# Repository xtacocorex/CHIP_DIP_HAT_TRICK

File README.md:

# CHIP_DIP_HAT_TRICK
CHIP DIP to allow users to attach PI Hats to their CHIP

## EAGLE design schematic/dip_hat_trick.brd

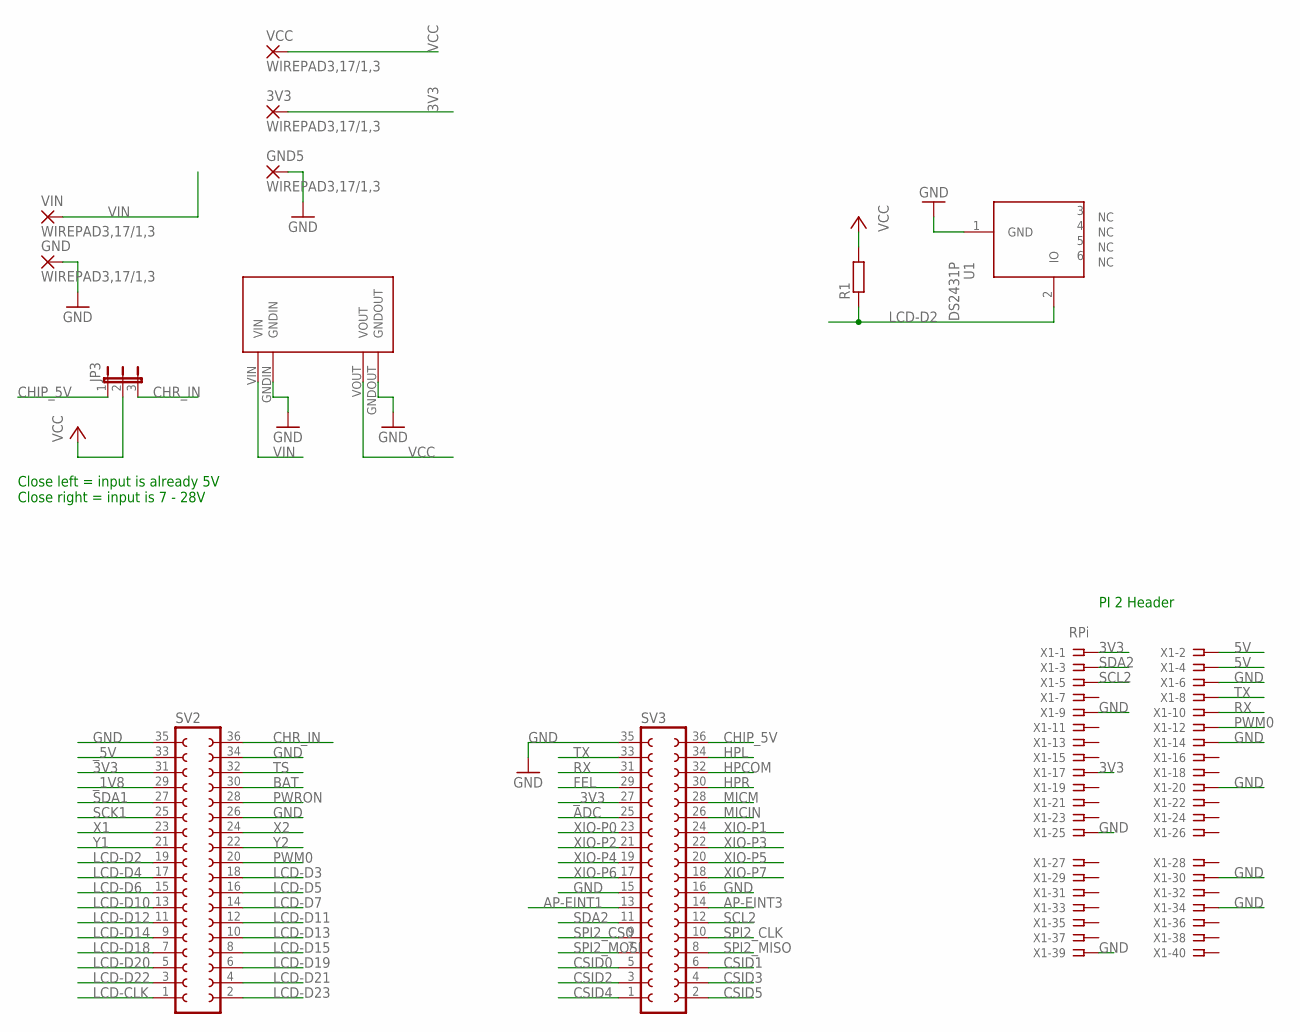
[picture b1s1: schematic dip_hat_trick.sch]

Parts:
3V3: WIREPAD3,17/1,3; 3,17/1,3
GND, GND5: WIREPAD3,17/1,3; 3,17/1,3
JP3: JP2E; JP2
R1: R-EU_R0805; R0805
SV2, SV3: FE18-2
U1: DS2431P; TSOC6
U$9: MP1584EN_FRAMELESS
VCC: WIREPAD3,17/1,3; 3,17/1,3
VIN: WIREPAD3,17/1,3; 3,17/1,3
X1: RPi; SSW-120-02-S-D

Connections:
3V3: 3V3.1, SV2.31, X1.1, X1.17
5V: X1.2, X1.4
ADC: SV3.25
AP-EINT1: SV3.13
AP-EINT3: SV3.14
BAT: SV2.30
CHIP_5V: JP3.1, SV3.36
CHR_IN: JP3.3, SV2.36
CSID0: SV3.5
CSID1: SV3.6
CSID2: SV3.3
CSID3: SV3.4
CSID4: SV3.1
CSID5: SV3.2
FEL: SV3.29
GND: GND.1, GND5.1, SV2.26, SV2.34, SV2.35, SV3.15, SV3.16, SV3.35, U1.1 (GND), U$9.GNDIN, U$9.GNDOUT, X1.6, X1.9, X1.14, X1.20, X1.25, X1.30, X1.34, X1.39
HPCOM: SV3.32
HPL: SV3.34
HPR: SV3.30
LCD-CLK: SV2.1
LCD-D2: R1.1, SV2.19, U1.2 (IO)
LCD-D3: SV2.18
LCD-D4: SV2.17
LCD-D5: SV2.16
LCD-D6: SV2.15
LCD-D7: SV2.14
LCD-D10: SV2.13
LCD-D11: SV2.12
LCD-D12: SV2.11
LCD-D13: SV2.10
LCD-D14: SV2.9
LCD-D15: SV2.8
LCD-D18: SV2.7
LCD-D19: SV2.6
LCD-D20: SV2.5
LCD-D21: SV2.4
LCD-D22: SV2.3
LCD-D23: SV2.2
MICIN: SV3.26
MICM: SV3.28
PWM0: SV2.20, X1.12
PWRON: SV2.28
RX: SV3.31, X1.10
SCK1: SV2.25
SCL2: SV3.12, X1.5
SDA1: SV2.27
SDA2: SV3.11, X1.3
SPI2_CLK: SV3.10
SPI2_CS0: SV3.9
SPI2_MISO: SV3.8
SPI2_MOSI: SV3.7
TS: SV2.32
TX: SV3.33, X1.8
VCC: JP3.2, R1.2, U$9.VOUT, VCC.1
VIN: U$9.VIN, VIN.1
X1: SV2.23
X2: SV2.24
XIO-P0: SV3.23
XIO-P1: SV3.24
XIO-P2: SV3.21
XIO-P3: SV3.22
XIO-P4: SV3.19
XIO-P5: SV3.20
XIO-P6: SV3.17
XIO-P7: SV3.18
Y1: SV2.21
Y2: SV2.22
_1V8: SV2.29
_3V3: SV3.27
_5V: SV2.33

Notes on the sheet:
Close left = input is already 5V Close right = input is 7 - 28V
PI 2 Header

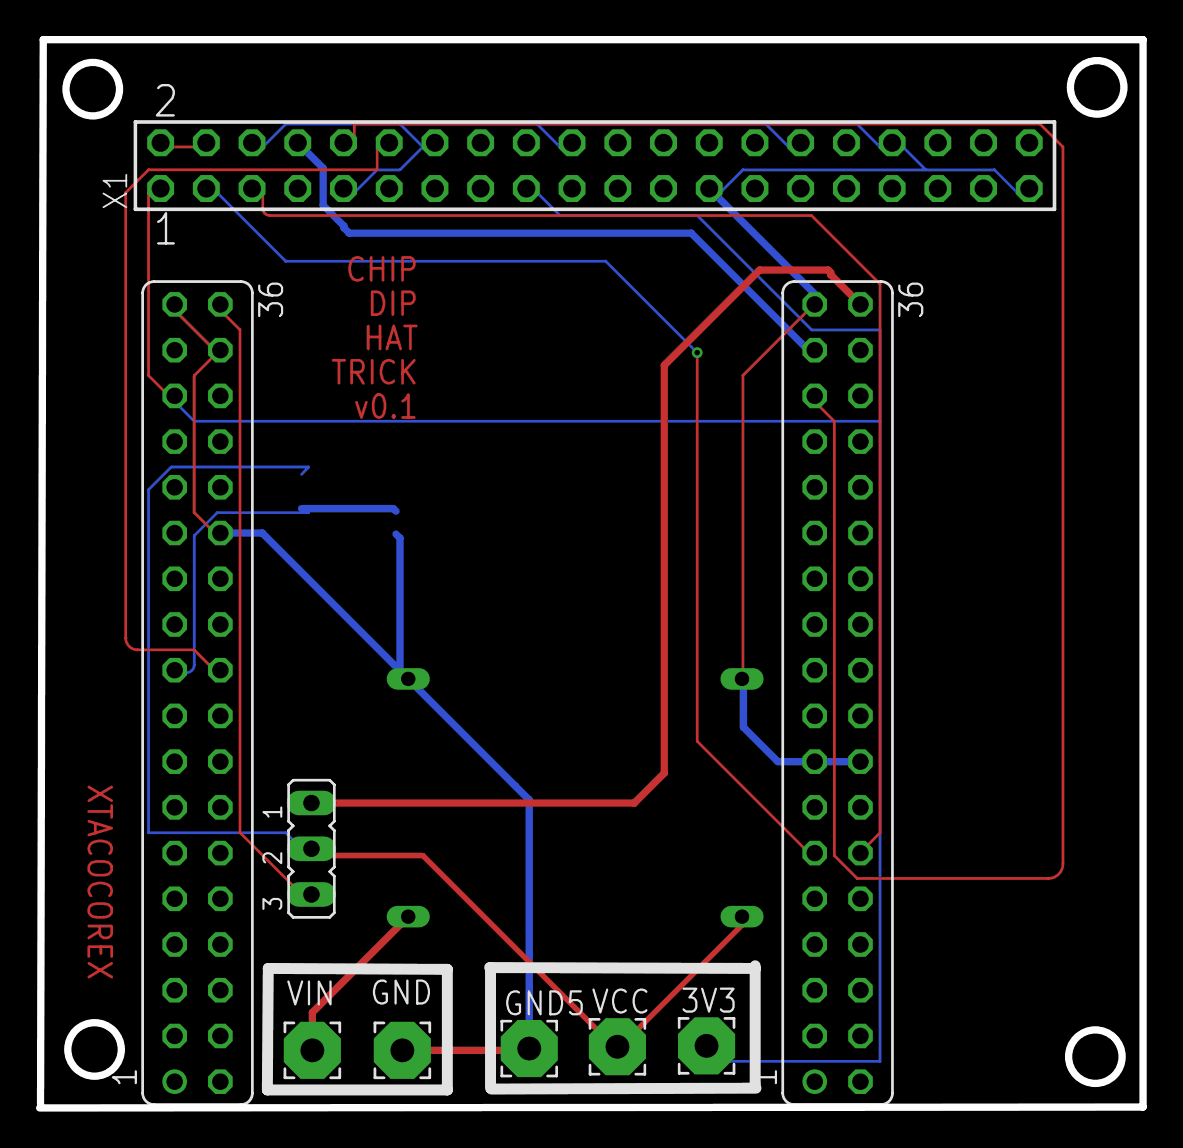
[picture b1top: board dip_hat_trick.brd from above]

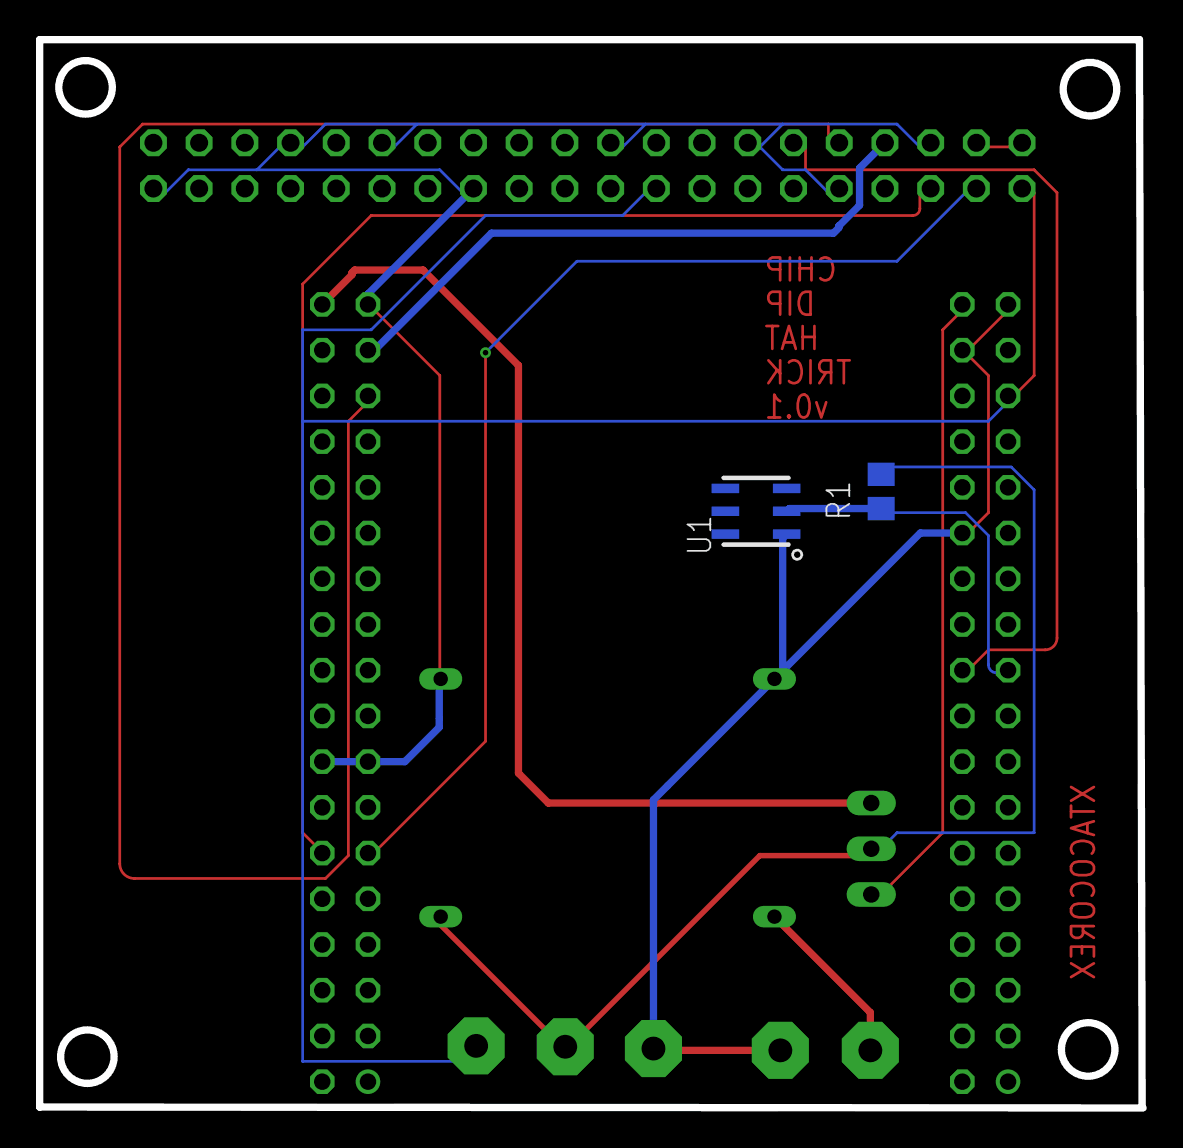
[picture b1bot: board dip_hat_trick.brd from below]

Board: 2 copper layers, 61.3 x 59.3 mm, 12 parts (2 on the bottom side), 13 nets.

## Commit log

2016-12-18 Initial commit of the Eagle Schematic and PCB Design
2016-12-18 Update to the DS2431 per info from @KoljaWindeler, Adding pdfs of the Schematic and PCB
